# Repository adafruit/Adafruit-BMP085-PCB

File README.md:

# PCB for the Adafruit 5V ready BMP085 Barometric

<a href="http://www.adafruit.com/products/391"><br/>Click here to purchase one from the Adafruit shop</a>

__Format is EagleCAD schematic and board layout__

This precision sensor from Bosch is the best low-cost sensing solution for measuring barometric pressure and temperature. Because pressure changes with altitude you can also use it as an altimeter! The sensor is soldered onto a PCB with a 3.3V regulator, I2C level shifter and pull-up resistors on the I2C pins.

__NEW! We now have a fully 5V compliant version of this board__ - a 3.3V regulator and a i2c level shifter circuit is included so you can use this sensor safely with 5V logic and power.

Using the sensor is easy. For example, if you're using an Arduino, simply connect the VIN pin to the 5V voltage pin, GND to ground, SCL to I2C Clock (Analog 5) and SDA to I2C Data (Analog 4). Then download our [BMP085 Arduino library and example code for temperature, pressure and altitude calculation](https://github.com/adafruit/Adafruit-BMP085-Library). Install the library, and load the example sketch. Immediately you'll have precision temperature, pressure and altitude data. [We also have a detailed tutorial so you can understand the sensor in depth](http://learn.adafruit.com/bmp085) including how to properly calculate altitude based on sea-level barometric pressure

## License
Adafruit invests time and resources providing this open source design,
please support Adafruit and open-source hardware by purchasing
products from Adafruit!

Designed by Adafruit Industries.
Creative Commons Attribution, Share-Alike license, check license.txt for more information
All text above must be included in any redistribution

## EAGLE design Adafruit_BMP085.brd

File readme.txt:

This is the PCB for the Adafruit 5V ready BMP085 Barometric 
Pressure/Temperature/Altitude Sensor

Format is EagleCAD schematic and board layout

For more details, check out the product page at

-----> https://www.adafruit.com/products/391

Adafruit invests time and resources providing this open source design, 
please support Adafruit and open-source hardware by purchasing 
products from Adafruit!

Designed by Adafruit Industries.  
Creative Commons Attribution, Share-Alike license, check license.txt for more information
All text above must be included in any redistribution

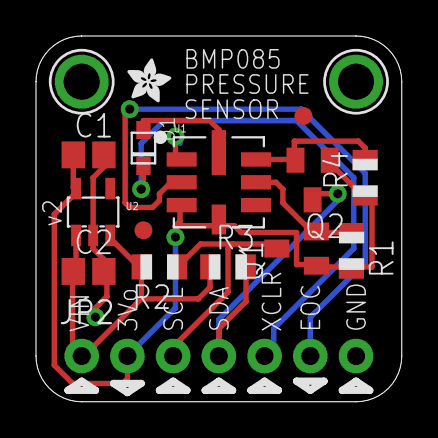
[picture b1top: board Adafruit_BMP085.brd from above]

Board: 2 copper layers, 20.3 x 20.3 mm, 18 parts (1 on the bottom side), 10 nets.

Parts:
C1, C2: 1.0uF; C0805
D1: 1N4148; SOD-323F
JP2: Breakout; 1X07_ROUND_76
Q1, Q2: BSS138; SOT23
R1, R2, R3, R4: 10K; R0805
U1: BMP085
U2: RT9193-33GB; SOT23-5
U$1, U$15: FIDUCIAL; FIDUCIAL_1MM
U$2, U$6: ADAFRUIT_2.5MM
U$7, U$8: MOUNTINGHOLE2.0; MOUNTINGHOLE_2.0_PLATED

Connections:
+3V3: C1.1, JP2.2, Q1.1, Q2.1, R1.2, R4.1, U1.P$3, U1.P$4, U2.5
+5V: C2.1, JP2.1, R2.2, R3.1, U2.1, U2.3
EOC: JP2.6, U1.P$2
GND: C1.2, C2.2, JP2.7, U1.P$1, U2.2
SCL_3.3V: Q1.2, R1.1, U1.P$6
SCL_5.0V: JP2.3, Q1.3, R2.1
SDA_3.3V: Q2.2, R4.2, U1.P$7
SDA_5.0V: JP2.4, Q2.3, R3.2
XCLR_3.3V: D1.A, U1.P$8
XCLR_5.0V: D1.C, JP2.5

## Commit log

2019-04-17 new readme + image
2026-06-03 update file format to XML
